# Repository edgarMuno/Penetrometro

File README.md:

# Penetrometro
Dispositivo para medir la compactacion de suelo, el resultado se vizualiza en una pantalla glcd 16x2 y puede ser guardada en un SD. El dispositivo se alimenta con una bateria recargable.

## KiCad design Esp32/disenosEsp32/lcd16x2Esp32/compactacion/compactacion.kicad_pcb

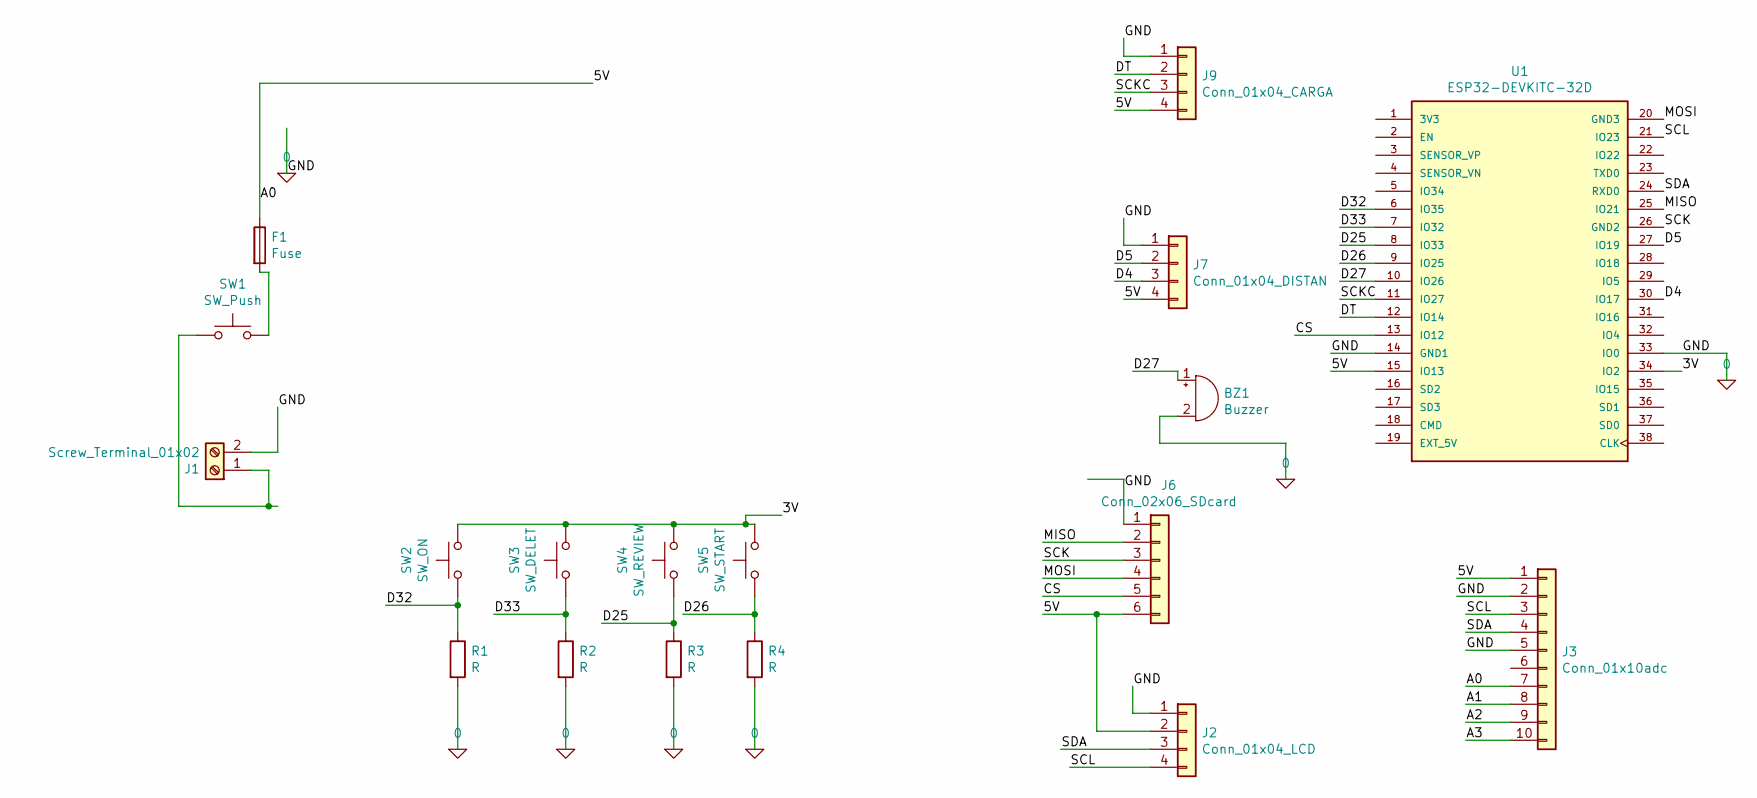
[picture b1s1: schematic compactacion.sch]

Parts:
BZ1: Buzzer; Buzzer_TDK_PS1240P02BT_D12.2mm_H6.5mm
F1: Fuse; Fuseholder_Cylinder-5x20mm_Schurter_0031_8201_Horizontal_Op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
J1: Screw_Terminal_01x02; TerminalBlock_bornier-2_P5.08mm
J2: Conn_01x04_LCD; FanPinHeader_1x04_P2.54mm_Vertical
J3: Conn_01x10adc; PinHeader_1x10_P2.54mm_Vertical
J6: Conn_02x06_SDcard; PinHeader_1x06_P2.54mm_Vertical
J7: Conn_01x04_DISTAN; FanPinHeader_1x04_P2.54mm_Vertical
J9: Conn_01x04_CARGA; FanPinHeader_1x04_P2.54mm_Vertical
R1, R2, R3, R4: R; R_Axial_DIN0207_L6.3mm_D2.5mm_P15.24mm_Horizontal
SW1: SW_Push; SW_DIP_SPSTx01_Piano_10.8x4.1mm_W7.62mm_P2.54mm
SW2: SW_ON; SW_PUSH_6mm_H4.3mm
SW3: SW_DELET; SW_PUSH_6mm_H4.3mm
SW4: SW_REVIEW; SW_PUSH_6mm_H4.3mm
SW5: SW_START; SW_PUSH_6mm_H4.3mm
U1: ESP32-DEVKITC-32D; MODULE_ESP32-DEVKITC-32D; PARTREV 4

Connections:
0: BZ1.2 (+), J1.2, J2.1, J3.2, J3.5, J6.1, J7.1, J9.1, R1.2, R2.2, R3.2, R4.2, U1.14 (GND1), U1.33 (IO0)
/3V: SW2.2, SW3.2, SW4.2, SW5.2, U1.34 (IO2)
/5V: F1.1, J2.2, J3.1, J3.7, J6.6, J7.4, J9.4, U1.15 (IO13)
/A1: J3.8
/A2: J3.9
/A3: J3.10
/CS: J6.5, U1.13 (IO12)
/D4: J7.3, U1.30 (IO17)
/D5: J7.2, U1.27 (IO19)
/D25: R3.1, SW4.1, U1.8 (IO33)
/D26: R4.1, SW5.1, U1.9 (IO25)
/D27: BZ1.1 (-), U1.10 (IO26)
/D32: R1.1, SW2.1, U1.6 (IO35)
/D33: R2.1, SW3.1, U1.7 (IO32)
/DT: J9.2, U1.12 (IO14)
/MISO: J6.2, U1.25 (IO21)
/MOSI: J6.4, U1.20 (GND3)
/SCK: J6.3, U1.26 (GND2)
/SCKC: J9.3, U1.11 (IO27)
/SCL: J2.4, J3.3, U1.21 (IO23)
/SDA: J2.3, J3.4, U1.24 (RXD0)
unnamed: F1.2, SW1.2
unnamed: J1.1, SW1.1

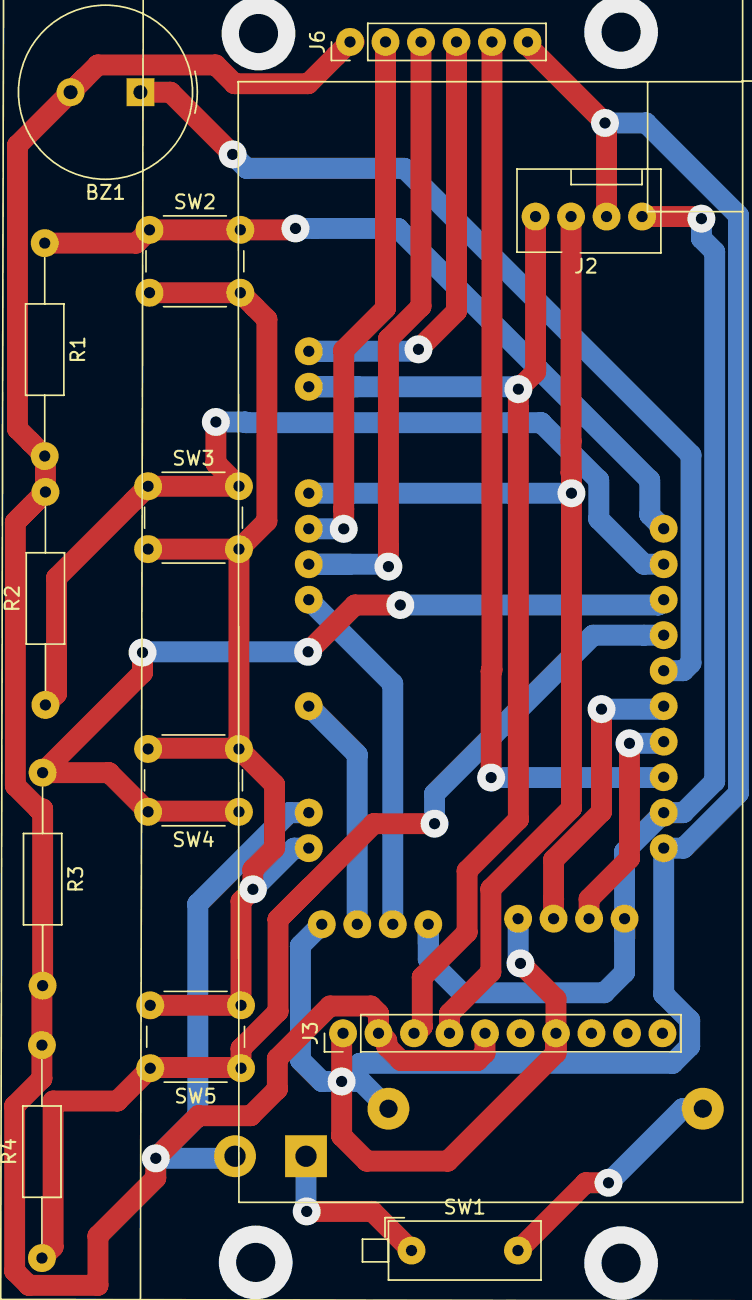
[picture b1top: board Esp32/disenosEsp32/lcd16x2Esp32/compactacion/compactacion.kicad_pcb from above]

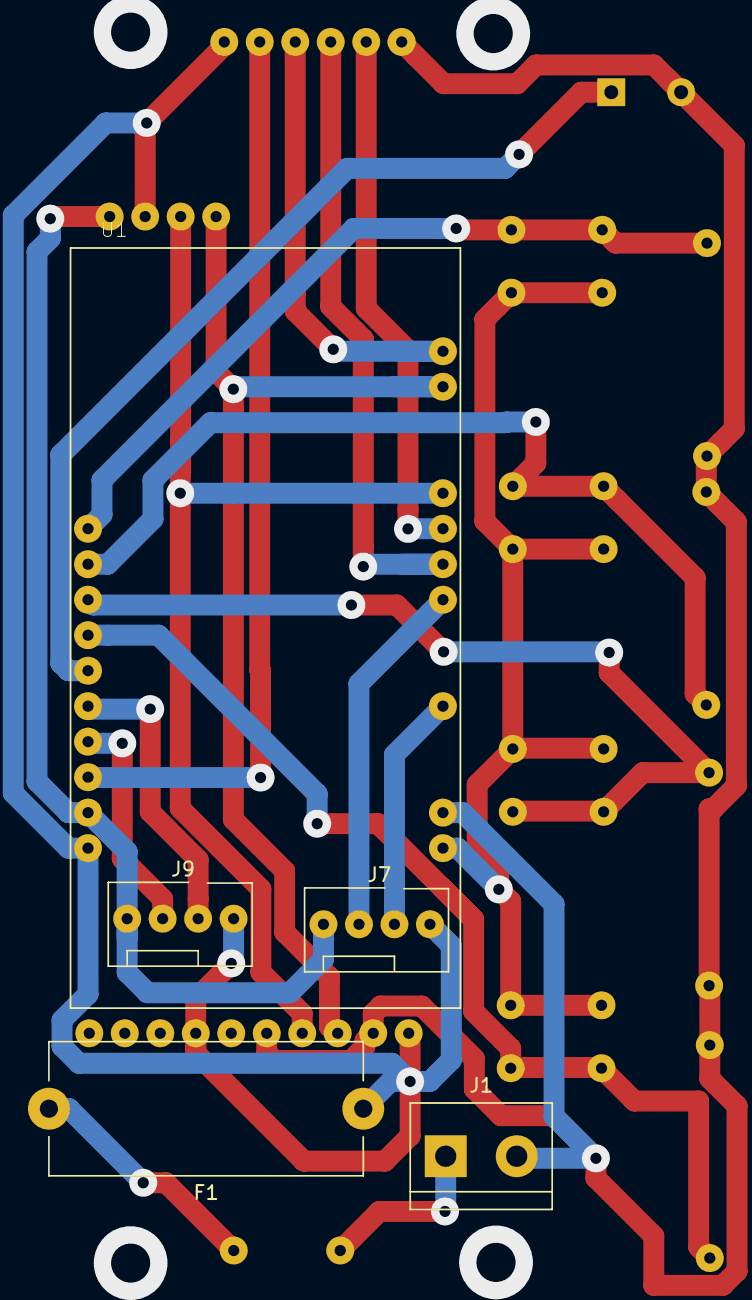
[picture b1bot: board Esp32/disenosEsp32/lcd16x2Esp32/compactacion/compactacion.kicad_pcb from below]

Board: 2 copper layers, 18 parts (5 on the bottom side), 20 nets.

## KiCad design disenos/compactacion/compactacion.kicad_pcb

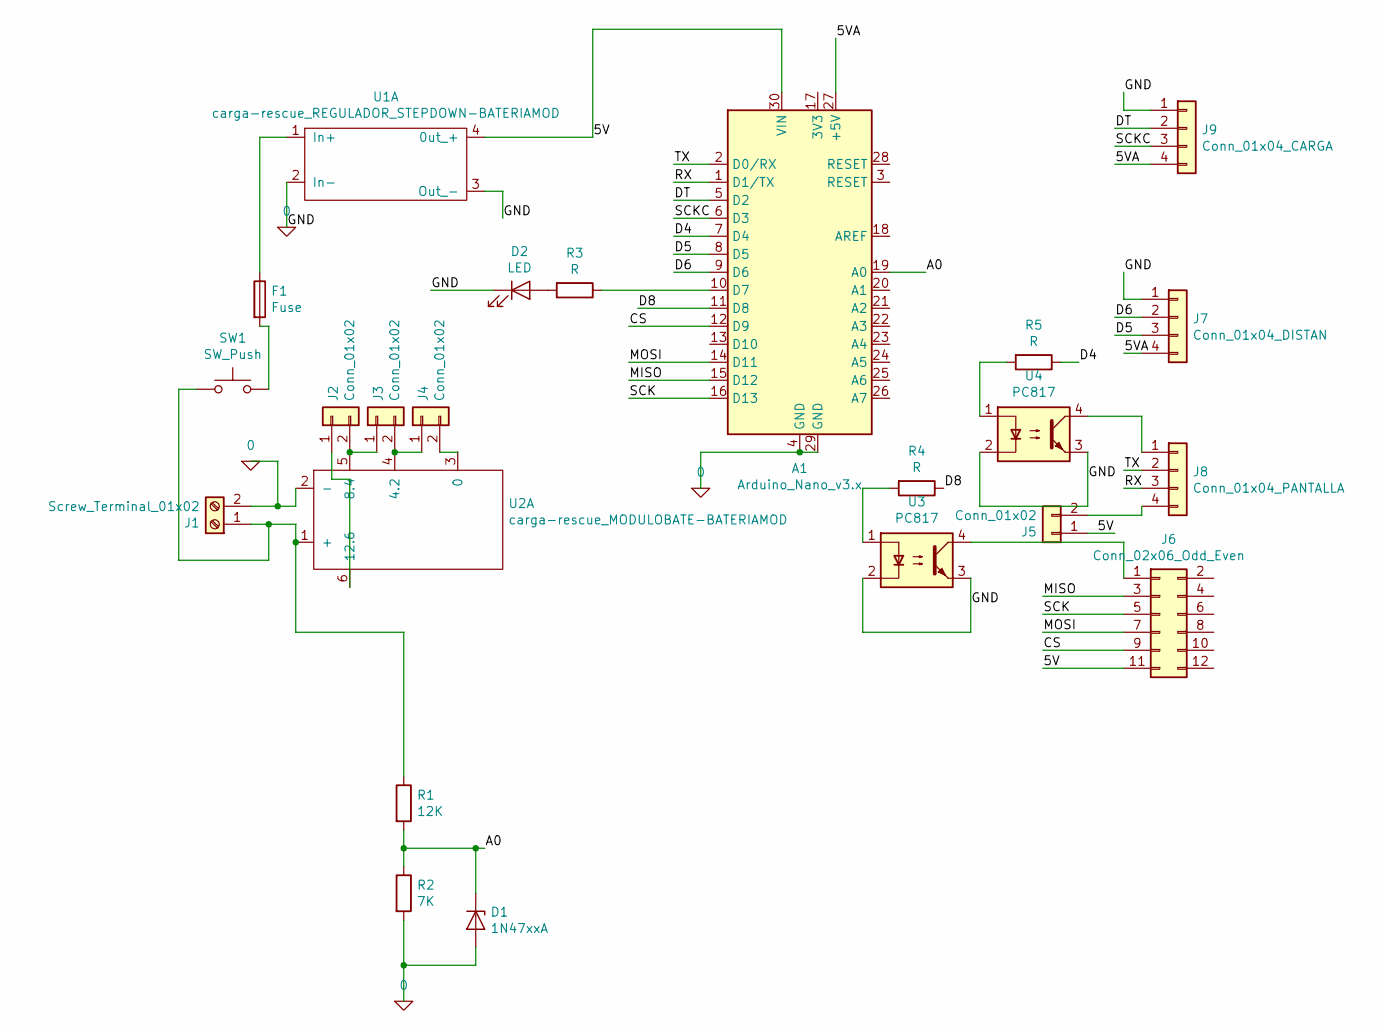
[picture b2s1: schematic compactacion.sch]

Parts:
A1: Arduino_Nano_v3.x; Arduino_Nano
D1: 1N47xxA; D_DO-41_SOD81_P10.16mm_Horizontal
D2: LED; LED_D3.0mm
F1: Fuse; Fuseholder_Cylinder-5x20mm_Schurter_0031_8201_Horizontal_Op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
J1: Screw_Terminal_01x02; TerminalBlock_bornier-2_P5.08mm
J2, J3, J4, J5: Conn_01x02; JST_XH_B2B-XH-A_1x02_P2.50mm_Vertical
J6: Conn_02x06_Odd_Even; IDC-Header_2x06_P2.54mm_Vertical
J7: Conn_01x04_DISTAN; FanPinHeader_1x04_P2.54mm_Vertical
J8: Conn_01x04_PANTALLA; FanPinHeader_1x04_P2.54mm_Vertical
J9: Conn_01x04_CARGA; FanPinHeader_1x04_P2.54mm_Vertical
R1: 12K; R_Axial_DIN0207_L6.3mm_D2.5mm_P15.24mm_Horizontal
R2: 7K; R_Axial_DIN0207_L6.3mm_D2.5mm_P15.24mm_Horizontal
R3, R4, R5: R; R_Axial_DIN0207_L6.3mm_D2.5mm_P15.24mm_Horizontal
SW1: SW_Push; SW_DIP_SPSTx01_Piano_10.8x4.1mm_W7.62mm_P2.54mm
U1: carga-rescue_REGULADOR_STEPDOWN-BATERIAMOD; REGULADOR STEP DOWN
U2: carga-rescue_MODULOBATE-BATERIAMOD; BATERIAMODULECHA
U3, U4: PC817; DIP-4_W7.62mm

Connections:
0: A1.4 (GND), A1.29 (GND), D1.2 (A), D2.1 (K), J1.2, J7.1, J9.1, R2.2, U1.2 (In-), U1.3 (Out_-), U2.2 (-), U3.2, U3.3, U4.2, U4.3
/5V: A1.30 (VIN), J5.1, J6.11, U1.4 (0ut_+)
/5VA: A1.27 (+5V), J7.4, J9.4
/A0: A1.19 (A0), D1.1 (K), R1.2, R2.1
/CS: A1.12 (D9), J6.9
/D4: A1.7 (D4), R5.1
/D5: A1.8 (D5), J7.3
/D6: A1.9 (D6), J7.2
/D8: A1.11 (D8), R4.1
/DT: A1.5 (D2), J9.2
/MISO: A1.15 (D12), J6.3
/MOSI: A1.14 (D11), J6.7
/RX: A1.1 (D1/TX), J8.3
/SCK: A1.16 (D13), J6.5
/SCKC: A1.6 (D3), J9.3
/TX: A1.2 (D0/RX), J8.2
unnamed: A1.10 (D7), R3.1
unnamed: D2.2 (A), R3.2
unnamed: F1.1, U1.1 (In+)
unnamed: F1.2, SW1.2
unnamed: J1.1, R1.1, SW1.1, U2.1 (+)
unnamed: J2.1, U2.6 (12.6)
unnamed: J2.2, J3.1, U2.5 (8.4)
unnamed: J3.2, J4.1, U2.4 (4.2)
unnamed: J4.2, U2.3 (0)
unnamed: J5.2, J8.4
unnamed: J6.1, U3.4
unnamed: J8.1, U4.4
unnamed: R4.2, U3.1
unnamed: R5.2, U4.1

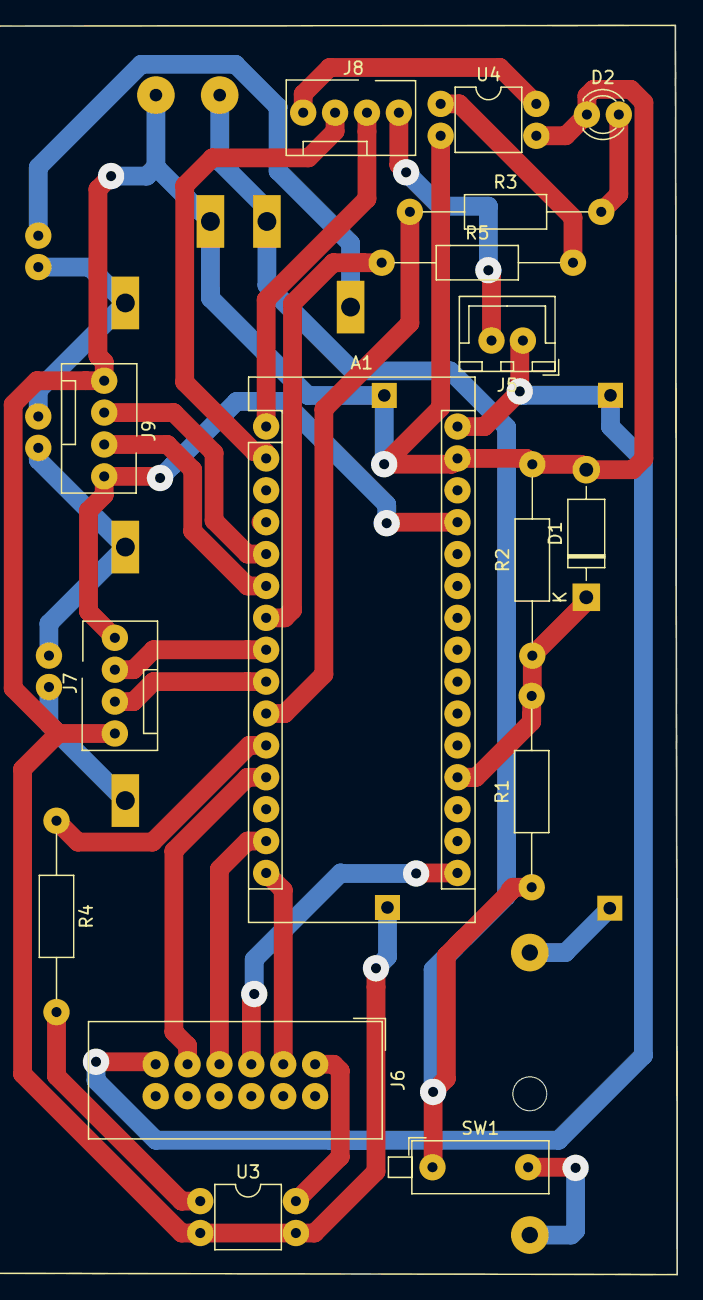
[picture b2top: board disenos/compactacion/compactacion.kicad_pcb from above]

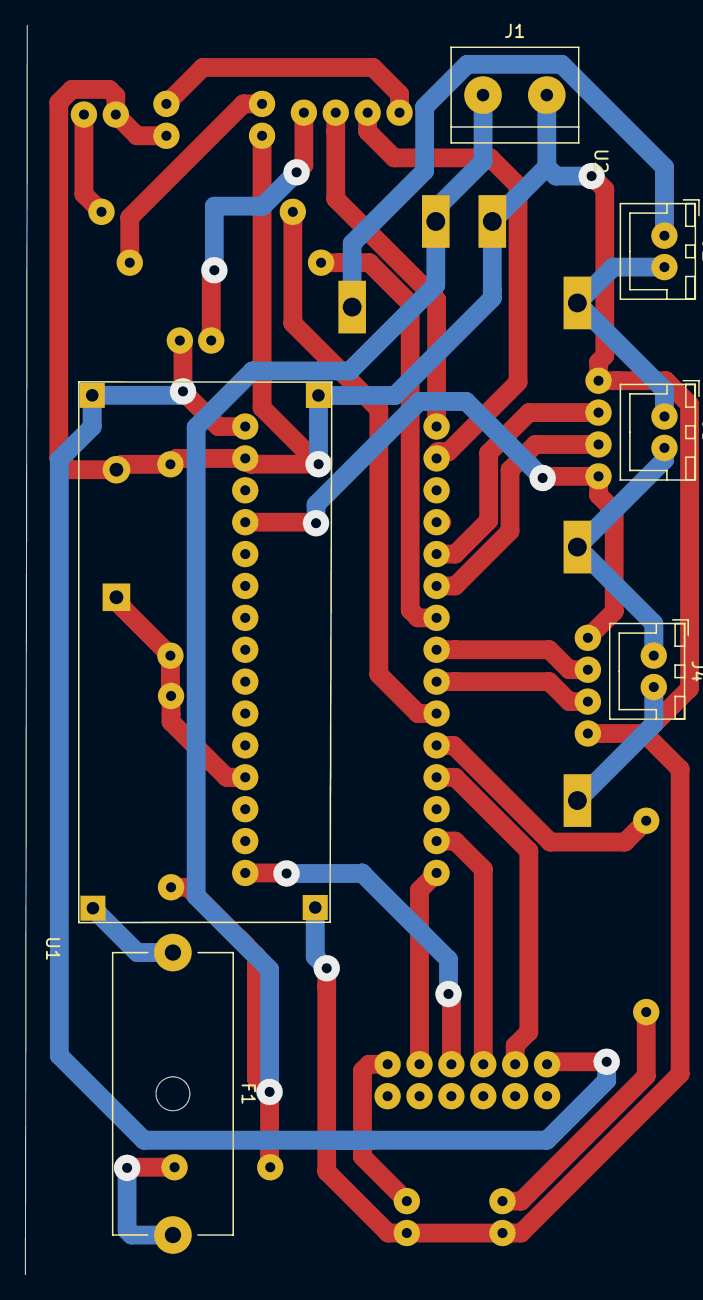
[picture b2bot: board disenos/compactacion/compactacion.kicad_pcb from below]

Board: 2 copper layers, 23 parts (7 on the bottom side), 30 nets.

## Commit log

2022-09-07 Add files via upload
    Version para Arduino Nano con pantalla LCD 16x2
2022-09-07 Add files via upload
    Codigo y disneos para ESP32 DEv MOD
